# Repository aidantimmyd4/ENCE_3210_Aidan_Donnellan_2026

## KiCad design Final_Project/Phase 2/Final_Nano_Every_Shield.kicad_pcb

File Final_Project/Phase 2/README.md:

# Microprocessors - Donnellan - Winter 2026
Final Project Phase 2 folder contains all files associated with the design of the Arduino Nano Every Atmospheric Ballon Shield.
Directory:
  - Components: All custom components made for shield.
  - Docs: Supporting documents showing schematic, PCB layout, footprint layout, and block diagrams.
  - gerber: All gerber files for manufacturing of PCB
  - .kicad_pcb, .kicad_sch, .kicad_pro, .kicad_prl program files
  - fp-info-cache and fp-lib-table
  - Pretty Folders: All custom footprints for board components.
  - Presentation: Design and component evaluation and choices associated with the Atmospheric Balloon Shield
Thank you for viewing!

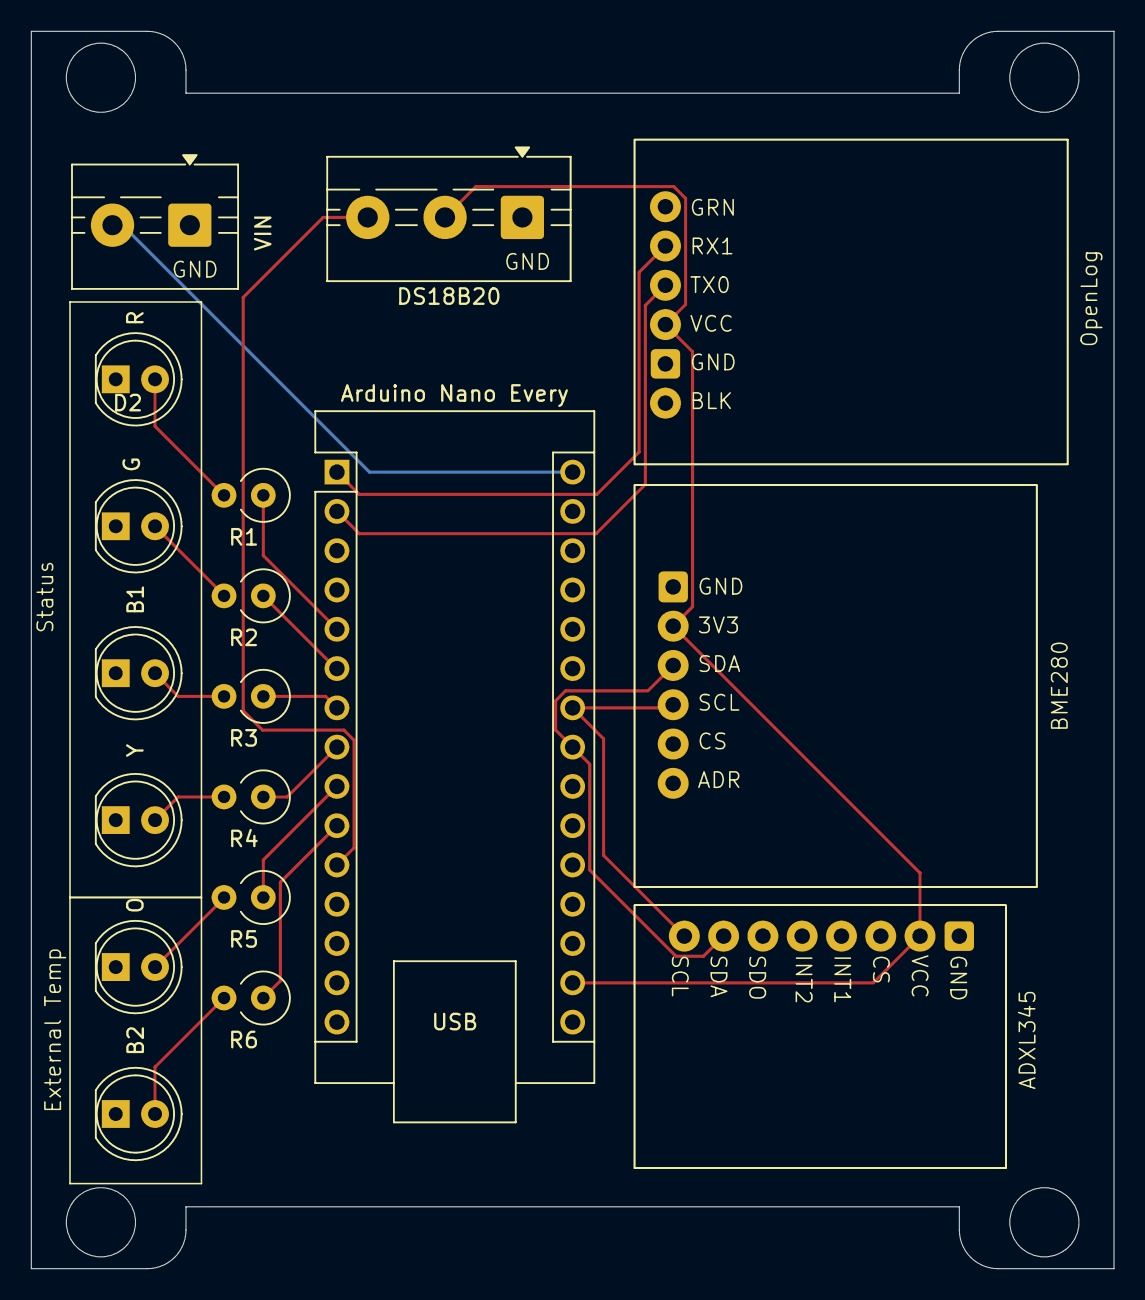
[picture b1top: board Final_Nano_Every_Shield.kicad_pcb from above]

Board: 2 copper layers, 70.0 x 80.0 mm, 18 parts (0 on the bottom side), 20 nets.

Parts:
Arduino Nano Every: Arduino_Nano_Every; Arduino_Nano
B1: Blue 1; LED_D5.0mm
B2: Blue 2; LED_D5.0mm
BME280: BME280; BME280_fp
D2: Green; LED_D5.0mm
DS18B20: Screw_Terminal_01x03; TerminalBlock_MaiXu_MX126-5.0-03P_1x03_P5.00mm
O: Orange; LED_D5.0mm
R: Red; LED_D5.0mm
R1, R2, R3, R4, R5, R6: 330; R_Axial_DIN0309_L9.0mm_D3.2mm_P2.54mm_Vertical
U2: ADXL345; ADXL_fp
U3: OpenLog; OpenLog_fp
VIN: Screw_Terminal_01x02; TerminalBlock_MaiXu_MX126-5.0-02P_1x02_P5.00mm
Y: Yellow; LED_D5.0mm

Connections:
+3V3: Arduino Nano Every.17 (3V3), BME280.2 (3V3), DS18B20.2, U2.2 (3V3), U3.4 (VCC)
/D2: Arduino Nano Every.5 (D2), R1.1
/D3: Arduino Nano Every.6 (D3), R2.1
/D4: Arduino Nano Every.7 (D4), R3.1
/D5: Arduino Nano Every.8 (D5), R4.1
/D6: Arduino Nano Every.9 (D6), R5.1
/D7: Arduino Nano Every.10 (D7), R6.1
/D8: Arduino Nano Every.11 (D8), DS18B20.3
/RX1: Arduino Nano Every.2 (RX1), U3.3 (TX0)
/SCL: Arduino Nano Every.24 (SCL/A5), BME280.4 (SCL), U2.8 (SCL)
/SDA: Arduino Nano Every.23 (SDA/A4), BME280.3 (SDA), U2.7 (SDA)
/TX1: Arduino Nano Every.1 (TX1), U3.2 (RX1)
/VIN: Arduino Nano Every.30 (VIN), VIN.2
GND: Arduino Nano Every.4 (GND), Arduino Nano Every.29 (GND), B1.1 (K), B2.1 (K), BME280.1 (GND), D2.1 (K), DS18B20.1, O.1 (K), R.1 (K), U2.1 (GND), U3.5 (GND), VIN.1, Y.1 (K)
unnamed: R.2 (A), R1.2
unnamed: D2.2 (A), R2.2
unnamed: B1.2 (A), R3.2
unnamed: R4.2, Y.2 (A)
unnamed: O.2 (A), R5.2
unnamed: B2.2 (A), R6.2

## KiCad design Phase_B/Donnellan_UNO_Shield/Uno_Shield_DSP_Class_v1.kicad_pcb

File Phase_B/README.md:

# Microprocessors - Winter Quarter 2026
# Aidan T. Donnellan
# This folder serves as the home for all Phase B material related to the course
# Thank you for viewing!

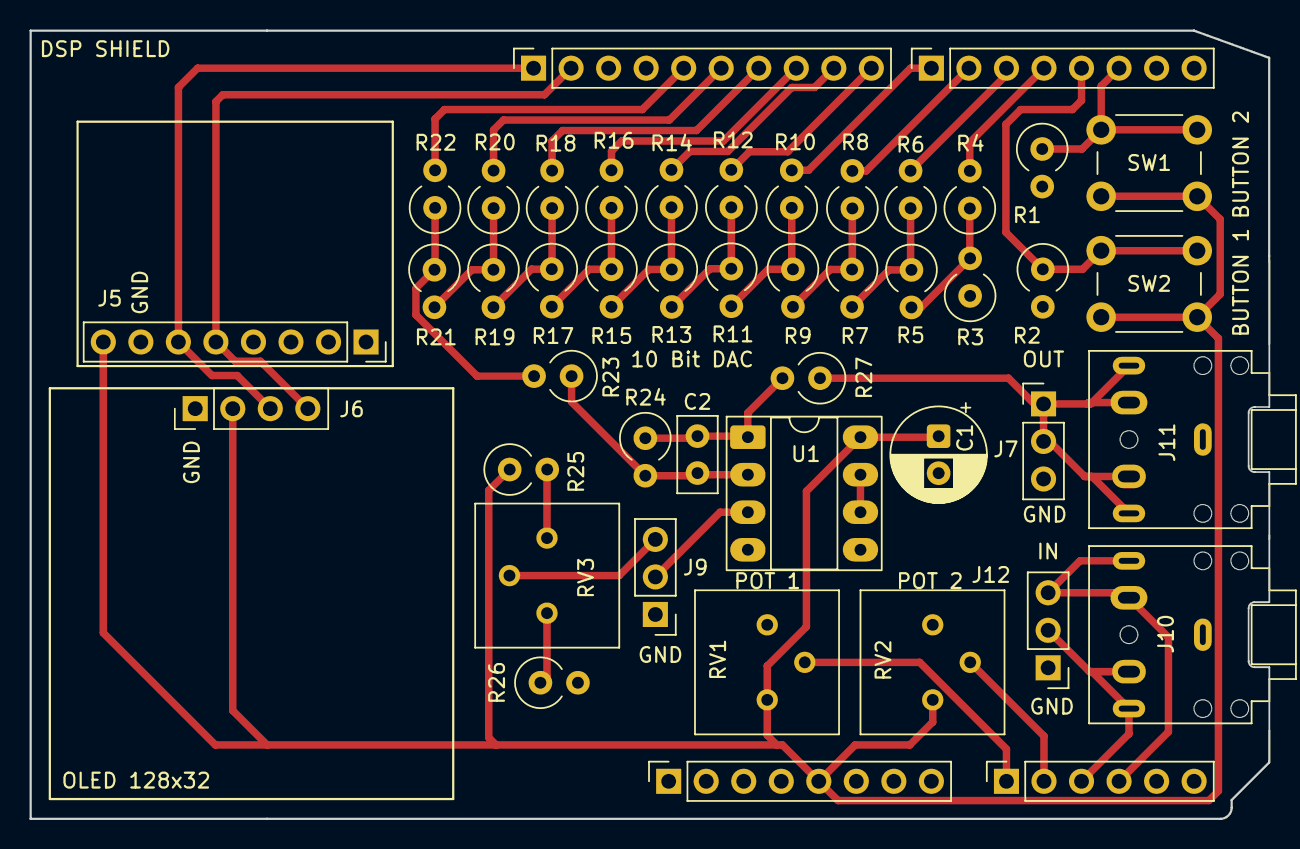
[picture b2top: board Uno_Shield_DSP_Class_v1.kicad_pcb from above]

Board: 2 copper layers, 83.8 x 53.3 mm, 46 parts (0 on the bottom side), 38 nets.

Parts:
C1: 47uF; CP_Radial_D6.3mm_P2.50mm
C2: 100pF; C_Disc_D5.0mm_W2.5mm_P2.50mm
J1: Power; PinSocket_1x08_P2.54mm_Vertical
J2: Digital/PWM; PinSocket_1x10_P2.54mm_Vertical
J3: Analog; PinSocket_1x06_P2.54mm_Vertical
J4: Digital/PWM; PinSocket_1x08_P2.54mm_Vertical
J5: IMU_CONN; PinSocket_1x08_P2.54mm_Vertical
J6: SCREEN_CONN; PinHeader_1x04_P2.54mm_Vertical
J7: AUDIO_OUT; PinHeader_1x03_P2.54mm_Vertical
J9: JUMPER; PinHeader_1x03_P2.54mm_Vertical
J10, J11: AudioJack5; Jack_3.5mm_CUI_SJ1-3525N_Horizontal
J12: AUDIO_IN; PinHeader_1x03_P2.54mm_Vertical
R1, R2: 100k; R_Axial_DIN0309_L9.0mm_D3.2mm_P2.54mm_Vertical
R3, R4, R6, R8, R10, R12, R14, R16, R18, R20, R22, R23, R24, R25, R26: 20k; R_Axial_DIN0309_L9.0mm_D3.2mm_P2.54mm_Vertical
R5, R7, R9, R11, R13, R15, R17, R19, R21: 10k; R_Axial_DIN0309_L9.0mm_D3.2mm_P2.54mm_Vertical
R27: 1k; R_Axial_DIN0309_L9.0mm_D3.2mm_P2.54mm_Vertical
RV1, RV2, RV3: 100k; Potentiometer_Bourns_3386P_Vertical
SW1: BT_1; SW_PUSH_6mm
SW2: BT_2; SW_PUSH_6mm
U1: MCP6002-xP; DIP-8_W7.62mm_Socket_LongPads

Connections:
+5V: C1.1, J1.5, J5.8, J6.2, R25.1, RV1.1, RV2.1, SW1.1, SW2.1, U1.8 (V+)
/A0: J3.1, RV1.2
/A1: J3.2, RV2.2
/AUDIO_OUT: J7.1, J7.2, J11.R, J11.RN, J11.T, J11.TN, R27.1
/BT1: J4.6, R1.1, SW1.2
/BT2: J4.5, R2.1, SW2.2
/D0: J4.4, R4.2
/D1: J4.3, R6.2
/D2: J4.2, R8.2
/D3: J4.1, R10.2
/D4: J2.10, R12.2
/D5: J2.9, R14.2
/D6: J2.8, R16.2
/D7: J2.7, R18.2
/D8: J2.6, R20.2
/D9: J2.5, R22.2
/IN_LEFT: J3.4, J10.T, J10.TN, J12.3
/IN_RIGHT: J3.3, J10.R, J10.RN, J12.2
/SCL: J2.1, J5.6, J6.3
/SDA: J2.2, J5.5, J6.4
GND: C1.2, J1.6, J1.7, J2.4, J5.7, J6.1, J7.3, J9.1, J10.S, J11.S, J12.1, R1.2, R2.2, R3.1, R26.2, RV1.3, RV2.3, U1.4 (V-), U1.5 (+)
unnamed: C2.2, R24.1, R27.2, U1.1
unnamed: J9.2, U1.3 (+)
unnamed: J9.3, RV3.2
unnamed: R3.2, R4.1, R5.2
unnamed: R5.1, R6.1, R7.2
unnamed: R7.1, R8.1, R9.2
unnamed: R9.1, R10.1, R11.2
unnamed: R11.1, R12.1, R13.2
unnamed: R13.1, R14.1, R15.2
unnamed: R15.1, R16.1, R17.2
unnamed: R17.1, R18.1, R19.2
unnamed: R19.1, R20.1, R21.2
unnamed: R21.1, R22.1, R23.2
unnamed: R25.2, RV3.1
unnamed: R26.1, RV3.3
unnamed: C2.1, R23.1, R24.2, U1.2 (-)
unnamed: U1.6 (-), U1.7

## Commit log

2026-01-09 Add my_file.txt with project notes
2026-01-11 Moved exercises into project folder
2026-01-11 Added Exercise 1.1 Code
2026-01-11 Added Math Exercise 1 code
2026-01-11 Added While Loop Testing 1 Code
2026-01-14 Lab 1 - Exercise 3
2026-01-14 Lab 1 - Exercise 5
2026-01-15 Added Lab 1 - Exercise 2
2026-01-16 Lab 1 - Exercise 7
2026-01-16 Lab 1 - Exercise 4
2026-01-16 Lab 1 - Exercise 1
2026-01-16 Lab 1 - Exercise 6
2026-01-16 Brief README file
2026-01-22 Lab 2 - Exercise 2
2026-01-22 Lab 2 - Exercise 4
2026-01-22 Lab 2 - Exercise 1
2026-01-22 README.md
2026-01-22 Lab 2 - Exercise 3
2026-01-30 Lab 3 Code
2026-01-30 Phase A labs moved to parent folder
2026-01-30 Cleaned up main Phase A folder
2026-01-30 Oscilloscope Captures for Phase B DAC
2026-01-30 Phase B Read Me
2026-01-30 Lab 3 Code Flowchart
2026-01-30 Hand Drawn Schematic of DAC tested in Lab 01/23/26
2026-01-30 Lab 3 Read Me
2026-02-02 Arduino UNO Shield KiCAD added to Phase_B Folder
2026-02-04 Revised version added, former version removed
2026-02-04 .step mv to docs/
2026-02-04 removed old .step location
2026-03-03 Phase C Documentation
2026-03-03 KiCAD PCD Model
2026-03-03 Added Readme
2026-03-03 Added Schematic
2026-03-05 PCB Assembly
2026-03-05 Block Diagram Added
2026-03-09 Phase 1 - Final Design Project
2026-03-09 DSP Shield Testing
2026-03-09 Corrected Testing Files
2026-03-09 Folder README
2026-03-12 Final Project KiCAD Design and Supporting Documents
2026-03-13 Add files via upload
    Revised Presentation
2026-03-13 Final Project Folder README
2026-03-13 Phase_1 README
